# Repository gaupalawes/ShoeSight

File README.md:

# Hours Taken till now: 5.6 hrs

Finally finished the schematic of the project after tons of issues. I used XIAO ESP32-C3 as a base microcontroller as it is small and works for my project fine. I use MPU-6050 as a accelerometer to detect any movements to solve any issue arise when the foot is in the midair while swinging. I used VL53LOC for the time of flight obstacle detector using lasers.

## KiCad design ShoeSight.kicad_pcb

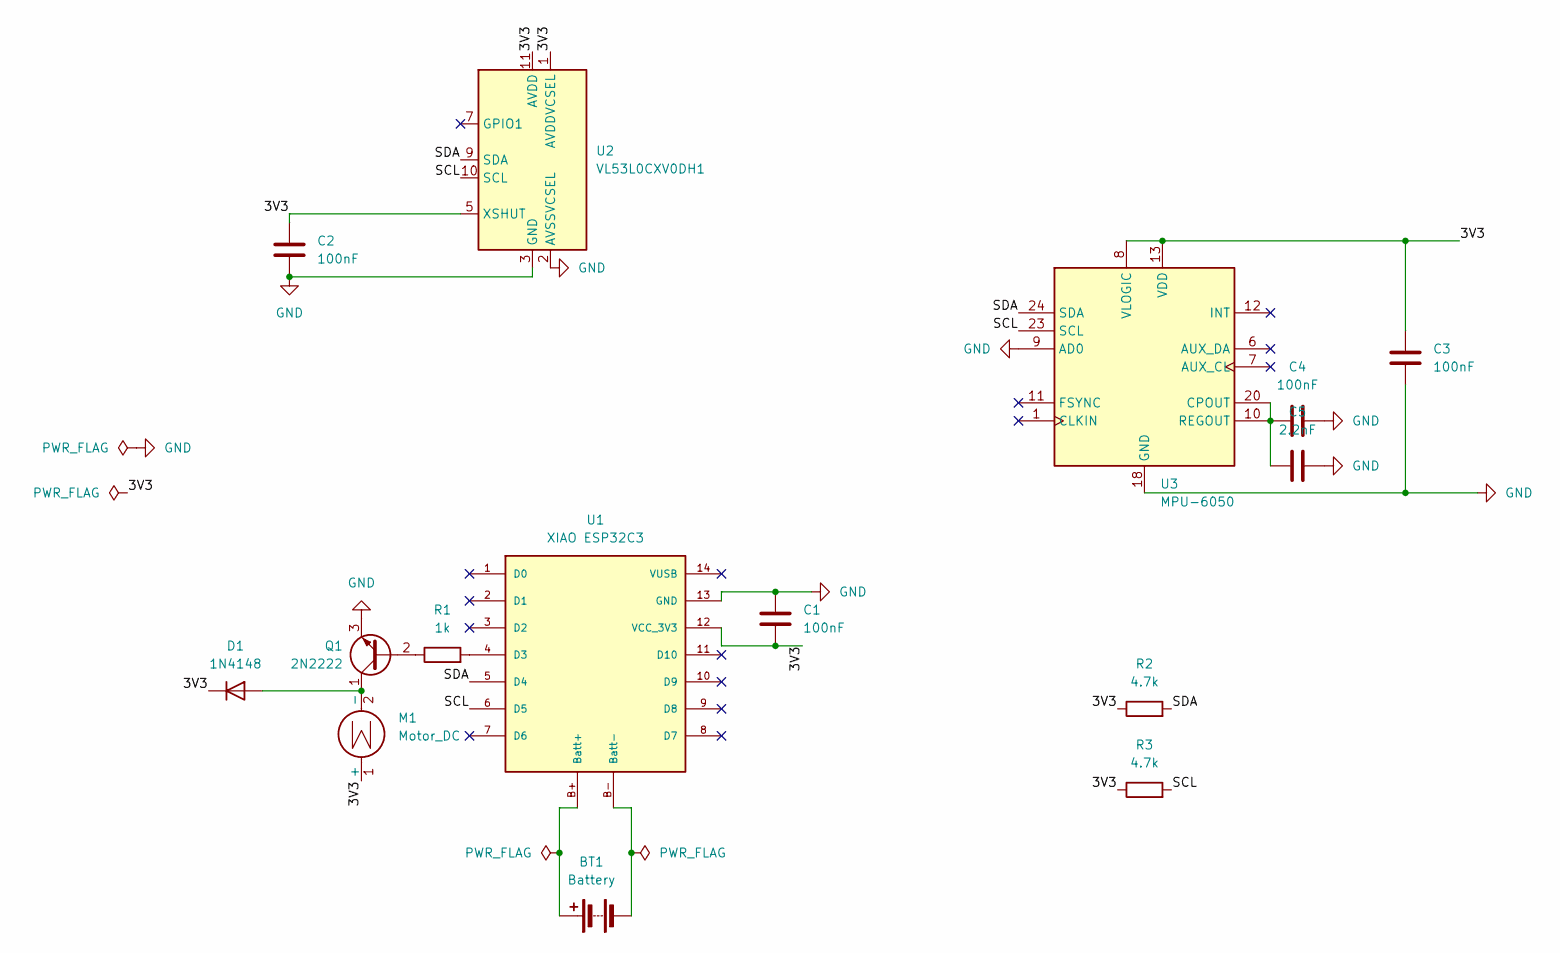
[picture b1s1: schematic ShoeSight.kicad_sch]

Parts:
BT1: Battery; JST_PH_B2B-PH-K_1x02_P2.00mm_Vertical
C1, C2, C3, C4: 100nF; C_0805_2012Metric
C5: 2.2nF; C_0805_2012Metric
D1: 1N4148; D_DO-35_SOD27_P7.62mm_Horizontal
M1: Motor_DC; PinHeader_1x02_P2.54mm_Vertical
Q1: 2N2222; TO-92_Inline
R1: 1k; R_0805_2012Metric
R2, R3: 4.7k; R_0805_2012Metric
U1: XIAO ESP32C3; xiao_esp32c3
U2: VL53L0CXV0DH1; ST_VL53L1x
U3: MPU-6050; InvenSense_QFN-24_4x4mm_P0.5mm

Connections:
/3V3: C1.2, C2.1, C3.1, D1.1 (K), M1.1 (+), R2.1, R3.1, U1.12 (VCC_3V3), U2.1 (AVDDVCSEL), U2.5 (XSHUT), U2.11 (AVDD), U3.8 (VLOGIC), U3.13 (VDD)
/SCL: R3.2, U1.6 (D5), U2.10 (SCL), U3.23 (SCL)
/SDA: R2.2, U1.5 (D4), U2.9 (SDA), U3.24 (SDA)
GND: C1.1, C2.2, C3.2, C4.2, C5.2, Q1.3 (E), U1.13 (GND), U2.2 (AVSSVCSEL), U2.3 (GND), U2.4 (GND), U2.6 (GND), U2.12 (GND), U3.9 (AD0), U3.18 (GND)
unnamed: BT1.1 (+), U1.B+ (Batt+)
unnamed: BT1.2 (-), U1.B- (Batt-)
unnamed: D1.2 (A), M1.2 (-), Q1.1 (C)
unnamed: Q1.2 (B), R1.1
unnamed: R1.2, U1.4 (D3)
unnamed: C4.1, C5.1, U3.10 (REGOUT), U3.20 (CPOUT)

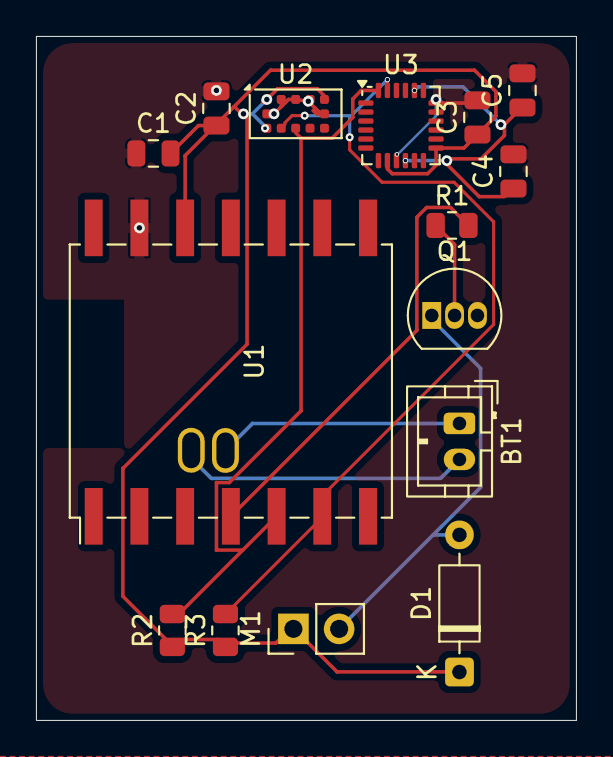
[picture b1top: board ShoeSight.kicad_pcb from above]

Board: 2 copper layers, 30.0 x 38.0 mm, 15 parts (0 on the bottom side), 10 nets.
